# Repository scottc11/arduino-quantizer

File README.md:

## LIBRARIES / DEPENDENCIES

#### [Adafruit MPR121](https://learn.adafruit.com/adafruit-mpr121-12-key-capacitive-touch-sensor-breakout-tutorial/overview)
- [eagle files can be found here](https://learn.sparkfun.com/tutorials/mpr121-hookup-guide)
#### [MCP4725 DAC](https://www.adafruit.com/product/935)

---
## QUANTIZER LOGIC

The QUANTIZER needs to output a single voltage relative to the last `touched` or `selected` (via voltage input)

The currently active notes will be toggled on / off via the touch sensors.

There is one touch sensor and one toggle switch for each `TONIC`.  Each `TONIC` will have a state equal to `major`, `minor`, `augmented`, and `diminished`. The state of each `TONIC`will be determined by their respective toggle switches.

The `Vout` will be determined depending on which `MODE` the quantizer is in:

`OUT MODE`: The last touched sensor
  - does not require `Vin`

`ARP MODE`:
  - the 'quantized' `Vin`
  - LEDs represent active notes `Vin` should be quantized to
  - does require `Vin`

Modular synths tend to follow a scheme were a specific change in voltage – such as 1.00 volts – results in a precisely one octave change in pitch. In a 1 volt per octave scheme, 1/12 of a volt change results in a semitone change in pitch.

```
5.00v == 5 octaves == 4095
1.00v == 1 octave == 819
0.08333v == half-tone == 68.25
0.16666v == whole-tone == 136.5
```

MCP4725 Library accepts input as a uint_t value between  0 to 4095

```
I    --> 1.0v ------>  819
II   --> 1.16666v -->  955.5
III  --> 1.33332v -->  1092
IV   --> 1.41665v -->  1160.25
V    --> 1.58331v -->  1296.75
VI   --> 1.74997v --> 1433.25
VII  --> 1.91663v --> 1569.75
VIII --> *2.0v    --> 1638

* round up to make perfect octave
```

### Quantization of `Vin` to `activeNotes`:
divide number of activeTonics by 1023. This will give you the thresholds for each note. Copy these thresholds to an array, from lowest to highest.
```

int activeCount = 0;
int activeNotes[];
int thresholdArray[];

for (int i=0; i<arrLength; i++) {
  if (activeTonics[i] == true) {
    activeNotes[activeCount] = quantizedVoltages[i];
    activeCount += 1;
  }
}
int threshold = 1023 / activeCount;
for (int i=0; i<activeCount; i++) {
  thresholdArray[i] = threshold * (i + 1);
}

for (int i=0; i<activeCount; i++) {
  if (Vin < thresholdArray[i]) {
    Vout = activeNotes[i];
  }
}
```

### Moog Werkstatt Calibration

Connect `Vout` of quantizer into the `VCO EXP IN` on the moog werkstatt.  You will have to remove the front panel of the werkstatt and modify the trimmer labelled `VCO EXP TRIM` so that 1.0v and 2.0v coming from `Vout` will make a perfect octave.  Use a tuner for this calibration.

---
# Arduino Programming Practices

#### Things to Note:
- Arduino code is essentially C/C++
- using dictionaries is pretty much out of the question due to memory limits

#### constants vs variables

constants don't take up valuable RAM space (the pre-processor subs the values in where needed), whereas variable declarations do.

```
// constants
#define VALUE_A 3
#define VALUE_B 1

// variables
int value_a = 3;
int value_b = 1;
```

#### [Charlieplexing](https://en.wikipedia.org/wiki/Charlieplexing)
- LED matrix
- Toggle Switch Matrix

---

# [I2C](https://learn.sparkfun.com/tutorials/i2c)

- I2C requires a mere two wires, like asynchronous serial, but those two wires can support up to 1008 slave devices.
- most I2C devices can communicate at 100kHz or 400kHz.
- It can be fairly trivially implemented in software.

#### Signals
- Each I2C bus consists of two signals: SCL and SDA. SCL is the clock signal, and SDA is the data signal.

---

# [Bitwise Operators](https://www.arduino.cc/reference/en/language/structure/bitwise-operators/bitwiseand/)
- One of the most common uses of bitwise AND is to select a particular bit (or bits) from an integer value, often called masking.
- [BitMath Tutorial](http://playground.arduino.cc/Code/BitMath)

In Arduino, the type int is a 16-bit value, so using & between two int expressions causes 16 simultaneous AND operations to occur.

```
int a =  92;    // in binary: 0000000001011100
int b = 101;    // in binary: 0000000001100101
int c = a & b;  // result:    0000000001000100, or 68 in decimal.
```
Each of the 16 bits in `a` and `b` are processed by using the bitwise AND, and all 16 resulting bits are stored in `c`, resulting in the value `01000100` in binary, which is `68` in decimal.

#### Common Bitwise Uses
- Saving memory by packing up to 8 true/false data values in a single byte.
- Turning on/off individual bits in a control register or hardware port register.
- Performing certain arithmetic operations involving multiplying or dividing by powers of 2.

###### Bitwise NOT operator

Bitwise NOT changes each bit to its opposite: 0 becomes 1, and 1 becomes 0. For example:
```
int a = 103;    // binary:  0000000001100111
int b = ~a;     // binary:  1111111110011000 = -104
```

###### Bit Shift Operators --> `>>` or `<<`
There are two bit shift operators in C++: the left shift operator `<<` and the right shift operator `>>`. These operators cause the bits in the left operand to be shifted left or right by the number of positions specified by the right operand. For example:
```
int a = 5;        // binary: 0000000000000101
int b = a << 3;   // binary: 0000000000101000, or 40 in decimal
int c = b >> 3;   // binary: 0000000000000101, or back to 5 like we started with
```
When you shift a value x by y bits (x << y), the leftmost y bits in x are lost, literally shifted out of existence.

### Port registers of the Atmega8

```
void setup()
{
  // set pins 1 (serial transmit) and 2..7 as output,
  // but leave pin 0 (serial receive) as input
  // (otherwise serial port will stop working!) ...
  DDRD = B11111110;  // digital pins 7,6,5,4,3,2,1,0

  // set pins 8..13 as output...
  DDRB = B00111111;  // digital pins -,-,13,12,11,10,9,8

  // Turn off digital output pins 2..7 ...
  PORTD &= B00000011;   // turns off 2..7, but leaves pins 0 and 1 alone

  // Write simultaneously to pins 8..13...
  PORTB = B00111000;   // turns on 13,12,11; turns off 10,9,8
}
```

Sometimes you might need to set multiple output pins at exactly the same time. Calling `digitalWrite(10,HIGH);` followed by `digitalWrite(11,HIGH);` will cause pin 10 to go `HIGH` several microseconds before pin 11, which may confuse certain time-sensitive external digital circuits you have hooked up. Alternatively, you could set both pins high at exactly the same moment in time using `PORTB |= B1100;`

------

### Button / Switch Logic

###### [Polling vs interrupts](http://www.martyncurrey.com/switching-things-on-and-off-with-an-arduino/)

<b>`Polling`</b> is where we are always checking the status of something. Inside the `loop()` function we continuously check the pin state with digitalRead(). We do not know if the pin state has changed until we look at it.

`Interrupts` is where the current process is interrupted and a new process is performed (the Arduino reacts to a pin state whether or not it is being checked). This means the code does not need to worry about the pin until the Arduino tells us to.

##### Turn LED On/Off with push button

```
int previousButtonState = LOW;

void loop() {
  int currentButtonState = cap.touched() & (1 << 0);

  if (currentButtonState == HIGH && oldButtonState == LOW) {
    // Switch the state of the output
    digitalWrite(ledPins[0], !digitalRead(ledPins[0]) );
  }

  previousButtonState = currentButtonState;
}
```

---

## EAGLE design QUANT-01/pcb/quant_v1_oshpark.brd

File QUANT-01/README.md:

### Components

- [SPDT Toggle Switch](https://www.digikey.ca/product-detail/en/e-switch/200MSP1T1B1M2QEH/EG2447-ND/378916)
- Arduino Pro Mini
- MPR121 Touch Matrix
- MCP4725 DAC
- LED x 8

# MODES

- when switching between modes, you have to somehjow preserve the previous modes active notes
- one way to do this is to store monophonic mode last touched Vout in a variable, and arpeggiator modes last count + active notes.

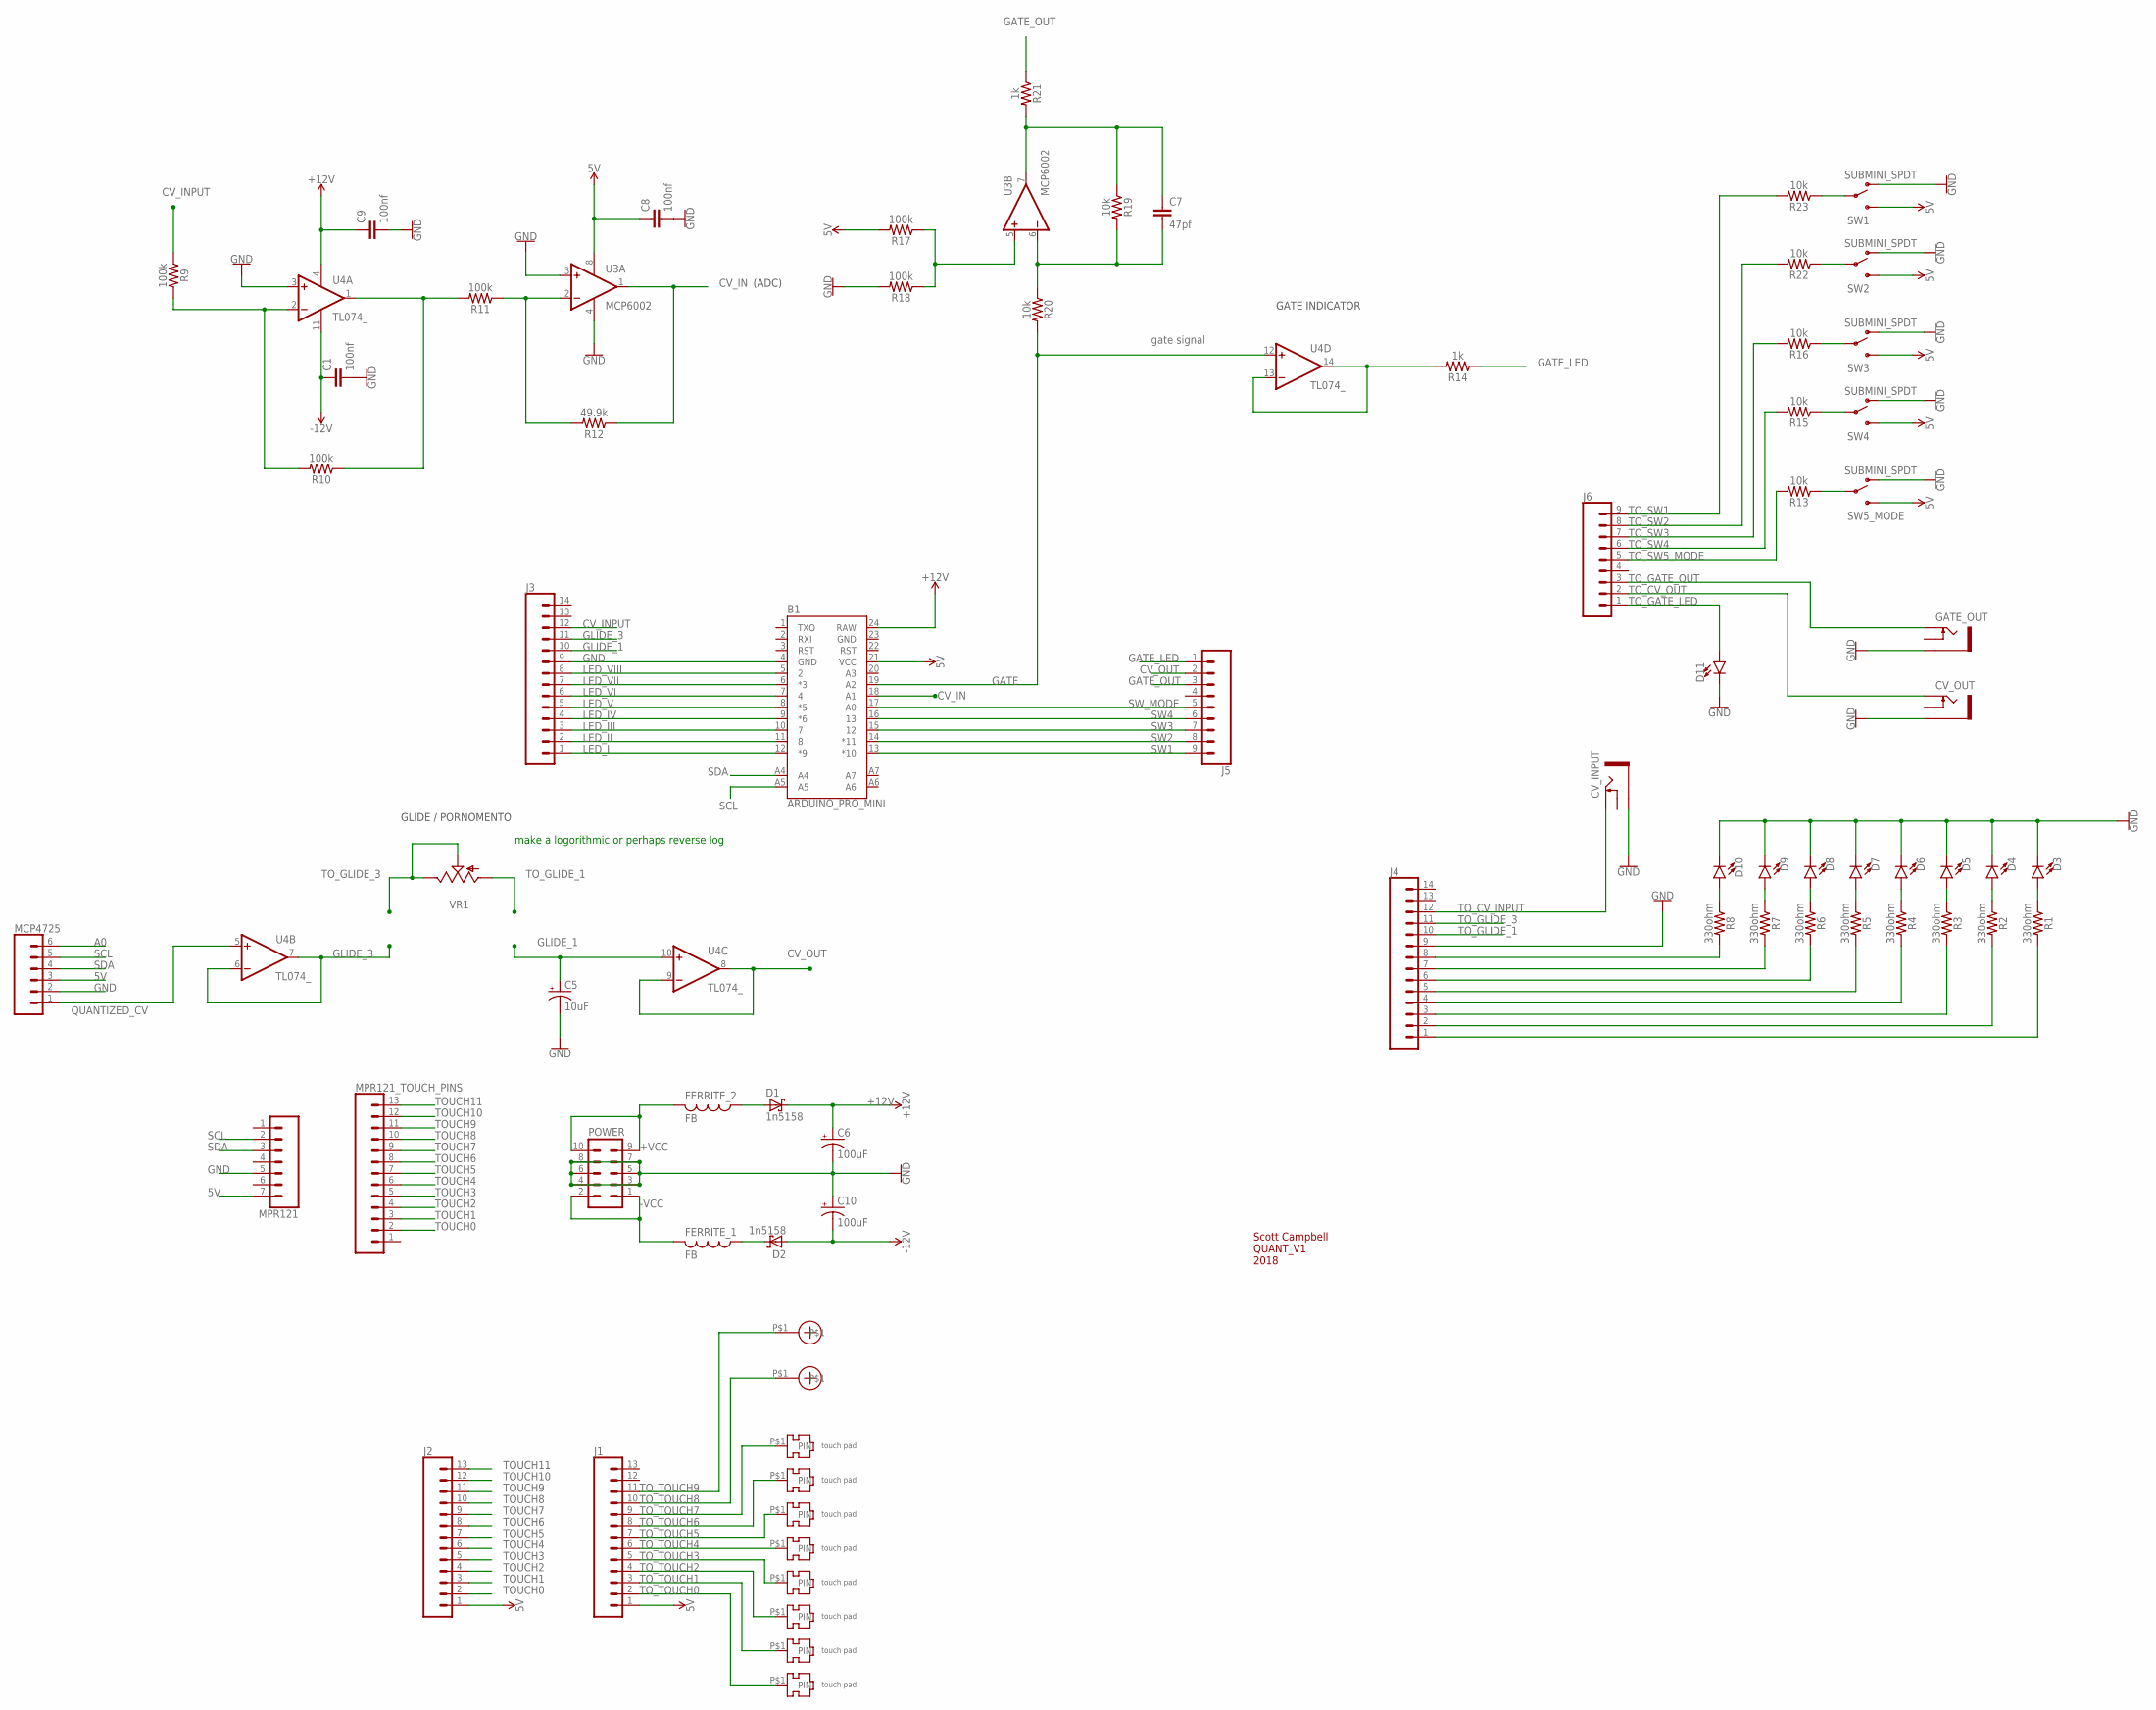
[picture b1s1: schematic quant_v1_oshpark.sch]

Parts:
B1: ARDUINO_PRO_MINI
C1, C9: 100nf; C2.5-5
C5: 10uF; CPOL-RADIAL-2.5MM-5MM
C6, C10: 100uF; CPOL-RADIAL-2.5MM-6.5MM
C7: 47pf; C2.5-5
C8: 100nf; C2.5-3
CV_INPUT: THONKICONNNEW; WQP-PJ301M-12_JACK
CV_OUT: CV_OUT; WQP-PJ301M-12_JACK
D1, D2: 1n5158; DO41-10
D3, D4, D5, D6, D7, D8, D9, D10, D11: LED3MM; LED_3MM
FERRITE_1, FERRITE_2: FB
GATE_OUT: GATE_OUT; WQP-PJ301M-12_JACK
J1, J2: CONN_13; 1X13
J3, J4: CONN_14; 1X14
J5, J6: CONN_09; 1X09
MCP4725: CONN_06NO_SILK_FEMALE_PTH; 1X06_NO_SILK
MPR121: CONN_07; 1X07
MPR121_TOUCH_PINS: CONN_13; 1X13
POWER: EURO_POWER_HEADERREGULAR; EURO_POWER_HEADER
R1, R2, R3, R4, R5, R6, R7, R8: 330ohm; AXIAL-0.3
R9, R10, R11, R17, R18: 100k; AXIAL-0.3
R12: 49.9k; AXIAL-0.3
R13, R15, R16, R19, R20, R22, R23: 10k; AXIAL-0.3
R14, R21: 1k; AXIAL-0.3
SW1, SW2, SW3, SW4, SW5_MODE: SUBMINI_SPDT; SUBMINI_TOGGLE
TOUCH_1, TOUCH_2, TOUCH_3, TOUCH_4, TOUCH_5, TOUCH_6, TOUCH_7, TOUCH_8: TOUCH_PAD_ESSY
U3: MCP6002; DIL08
U4: TL074_; DIL14
U$1, U$2: TOUCH_PAD_INCREMENT
VR1: 9MM_SNAP-IN_POT_; 9MM_SNAP-IN_POT

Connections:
5V: B1.21 (VCC), C8.1, J1.1, J2.1, MCP4725.3, MPR121.7, R17.P$2 (2), SW1.3 (S), SW2.3 (S), SW3.3 (S), SW4.3 (S), U3.8 (V+)
+12V: B1.24 (RAW), C6.1 (+), C9.1, D1.C, U4.4 (V+)
+VCC: FERRITE_2.P$2 (2), POWER.9, POWER.10
-12V: C1.1, C10.2 (-), D2.A, U4.11 (V-)
-VCC: FERRITE_1.P$2 (2), POWER.1, POWER.2
A0: MCP4725.6
CV_IN: B1.18 (A1), R12.P$1 (1), U3.1 (OUT)
CV_INPUT: J3.12, R9.P$1 (1)
CV_OUT: J5.2, U4.8 (OUT), U4.9 (-IN)
GATE: B1.19 (A2), R20.P$2 (2), U4.12 (+IN)
GATE_LED: J5.1, R14.P$1 (1)
GATE_OUT: J5.3, R21.P$1 (1)
GLIDE_1: C5.1 (+), J3.10, U4.10 (+IN)
GLIDE_3: J3.11, U4.6 (-IN), U4.7 (OUT)
GND: B1.4 (GND), B1.23 (GND), C1.2, C5.2 (-), C6.2 (-), C8.2, C9.2, C10.1 (+), CV_INPUT.P$3_SLEEVE (SLEEVE), CV_OUT.P$3_SLEEVE (SLEEVE), D3.K (C), D4.K (C), D5.K (C), D6.K (C), D7.K (C), D8.K (C), D9.K (C), D10.K (C), D11.K (C), GATE_OUT.P$3_SLEEVE (SLEEVE), J3.9, J4.9, MCP4725.2, MPR121.5, POWER.3, POWER.4, POWER.5, POWER.6, POWER.7, POWER.8, R18.P$2 (2), SW1.1 (O), SW2.1 (O), SW3.1 (O), SW4.1 (O), SW5_MODE.1 (O), U3.3 (+IN), U3.4 (V-), U4.3 (+IN)
LED_I: B1.12 (*9), J3.1
LED_II: B1.11 (8), J3.2
LED_III: B1.10 (7), J3.3
LED_IV: B1.9 (*6), J3.4
LED_V: B1.8 (*5), J3.5
LED_VI: B1.7 (4), J3.6
LED_VII: B1.6 (*3), J3.7
LED_VIII: B1.5 (2), J3.8
unnamed: D2.C, FERRITE_1.P$1 (1)
unnamed: C7.1, R19.P$1 (1), R21.P$2 (2), U3.7 (OUT)
unnamed: D1.A, FERRITE_2.P$1 (1)
unnamed: R23.P$1 (1), SW1.COM (COMMON)
unnamed: D3.A, R1.P$1 (1)
unnamed: R22.P$1 (1), SW2.COM (COMMON)
unnamed: R16.P$1 (1), SW3.COM (COMMON)
unnamed: R15.P$1 (1), SW4.COM (COMMON)
unnamed: R14.P$2 (2), U4.13 (-IN), U4.14 (OUT)
unnamed: D10.A, R8.P$1 (1)
unnamed: D9.A, R7.P$1 (1)
unnamed: D8.A, R6.P$1 (1)
unnamed: D7.A, R5.P$1 (1)
unnamed: D6.A, R4.P$1 (1)
unnamed: D5.A, R3.P$1 (1)
unnamed: D4.A, R2.P$1 (1)
unnamed: C7.2, R19.P$2 (2), R20.P$1 (1), U3.6 (-IN)
unnamed: R9.P$2 (2), R10.P$2 (2), U4.2 (-IN)
unnamed: R13.P$1 (1), SW5_MODE.COM (COMMON)
unnamed: R10.P$1 (1), R11.P$2 (2), U4.1 (OUT)
unnamed: R11.P$1 (1), R12.P$2 (2), U3.2 (-IN)
unnamed: R17.P$1 (1), R18.P$1 (1), U3.5 (+IN)
unnamed: J4.8, R8.P$2 (2)
unnamed: J4.7, R7.P$2 (2)
unnamed: J4.6, R6.P$2 (2)
unnamed: J4.5, R5.P$2 (2)
unnamed: J4.4, R4.P$2 (2)
unnamed: J4.3, R3.P$2 (2)
unnamed: J4.2, R2.P$2 (2)
unnamed: J4.1, R1.P$2 (2)
QUANTIZED_CV: MCP4725.1, U4.5 (+IN)
SCL: B1.A5, MCP4725.5, MPR121.2
SDA: B1.A4, MCP4725.4, MPR121.3
SW1: B1.13 (*10), J5.9
SW2: B1.14 (*11), J5.8
SW3: B1.15 (12), J5.7
SW4: B1.16 (13), J5.6
SW_MODE: B1.17 (A0), J5.5
TOUCH0: J2.2, MPR121_TOUCH_PINS.2
TOUCH1: J2.3, MPR121_TOUCH_PINS.3
TOUCH2: J2.4, MPR121_TOUCH_PINS.4
TOUCH3: J2.5, MPR121_TOUCH_PINS.5
TOUCH4: J2.6, MPR121_TOUCH_PINS.6
TOUCH5: J2.7, MPR121_TOUCH_PINS.7
TOUCH6: J2.8, MPR121_TOUCH_PINS.8
TOUCH7: J2.9, MPR121_TOUCH_PINS.9
TOUCH8: J2.10, MPR121_TOUCH_PINS.10
TOUCH9: J2.11, MPR121_TOUCH_PINS.11
TOUCH10: J2.12, MPR121_TOUCH_PINS.12
TOUCH11: J2.13, MPR121_TOUCH_PINS.13
TO_CV_INPUT: CV_INPUT.P$1_TIP (TIP), J4.12
TO_CV_OUT: CV_OUT.P$1_TIP (TIP), J6.2
TO_GATE_LED: D11.A, J6.1
TO_GATE_OUT: GATE_OUT.P$1_TIP (TIP), J6.3
TO_GLIDE_1: J4.10, VR1.1 (A)
TO_GLIDE_3: J4.11, VR1.2 (S), VR1.3 (E)
TO_SW1: J6.9, R23.P$2 (2)
TO_SW2: J6.8, R22.P$2 (2)
TO_SW3: J6.7, R16.P$2 (2)
TO_SW4: J6.6, R15.P$2 (2)
TO_SW5_MODE: J6.5, R13.P$2 (2)
TO_TOUCH0: J1.2, TOUCH_8.P$1
TO_TOUCH1: J1.3, TOUCH_7.P$1
TO_TOUCH2: J1.4, TOUCH_6.P$1
TO_TOUCH3: J1.5, TOUCH_5.P$1
TO_TOUCH4: J1.6, TOUCH_4.P$1
TO_TOUCH5: J1.7, TOUCH_3.P$1
TO_TOUCH6: J1.8, TOUCH_2.P$1
TO_TOUCH7: J1.9, TOUCH_1.P$1
TO_TOUCH8: J1.10, U$2.P$1
TO_TOUCH9: J1.11, U$1.P$1

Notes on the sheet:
Scott Campbell QUANT_V1 2018
GLIDE / PORNOMENTO
GATE INDICATOR
gate signal
(ADC)
make a logorithmic or perhaps reverse log

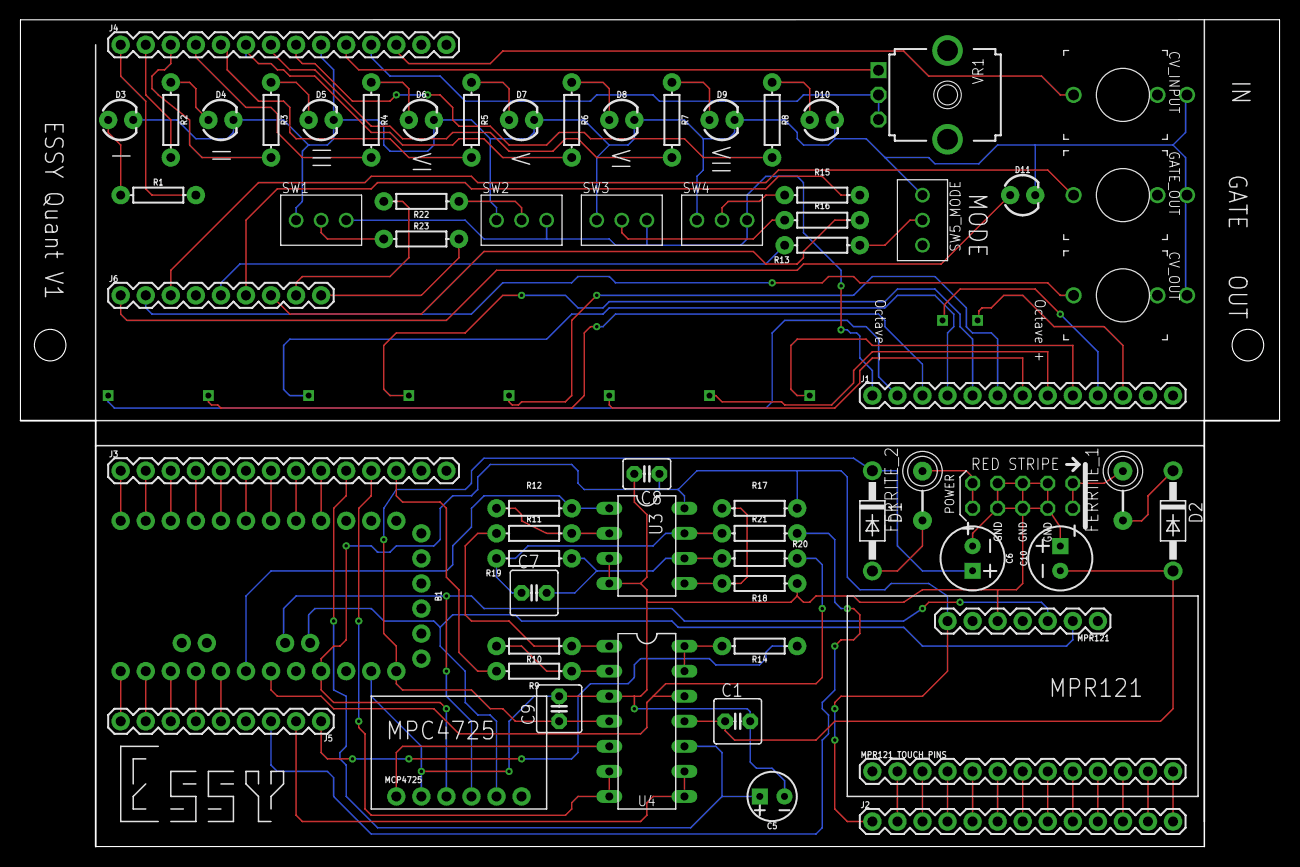
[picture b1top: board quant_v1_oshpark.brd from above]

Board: 2 copper layers, 127.6 x 83.7 mm, 77 parts (0 on the bottom side), 93 nets.

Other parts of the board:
U$3, U$4: EURO_PANEL_SCREW_HOLE

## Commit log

2018-03-25 added git ignore.
2018-03-25 moved file into folder.
2018-03-26 setup the DAC code testing code.
2018-03-29 DAC is now outputting proper voltages per semitone
2018-03-30 setup base quantizer arduino sketch.
2018-03-30 implemented the tonic scale system using set values for voltages of a major scale.
2018-03-30 established tonic status on / off toggle
2018-03-30 added schematic.
2018-03-30 kind of got the quantization of Vin working.
2018-03-30 fixed arpegiator bug causing awfull quantization by adding a break statement
2018-03-30 successfully added toggle switch states to code allowing for major/minor mods
2018-03-31 added eagle fold pcb. moved schematic file into that new folder. created base perf board file,
2018-04-01 built the base schematic.
2018-04-05 renamed some variable names for better readability.
2018-04-05 switched to new branch.
2018-04-06 got monophonic mode working. Note changes are not as responsive as I would like.
2018-04-06 implmemented mode logic gates. each mode works respectively.
2018-04-06 added a comment.
2018-04-07 fixed tonic switch bug
2018-04-07 established mode switching while persisting active notes for each mode between switches.
2018-04-07 added a last touched variable for monophonic so that when a tonic changes the change will be immediately applied.
2018-04-08 added simple GATE out code.
2018-04-10 started building board.
2018-04-11 got bottom pcb basic layout in place.
2018-04-12 started wiring.
2018-04-15 starting wiring. completed layout of components.
2018-05-26 completed first PCB run with OSH park. Beginning to make mods to add octaves.
2018-06-13 fixed formula for increasing / decreasing octave
2018-06-13 added remaining tonic toggle switches. Switched some pins around to match schematic. Currently a stable build.

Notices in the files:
parts and their libraries:
SparkFun-Boards: Licensing: Creative Commons ShareAlike 4.0 International - https://creativecommons.org/licenses/by-sa/4.0
